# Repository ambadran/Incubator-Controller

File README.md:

# Incubator-Controller

PCB Circuit to interface all the incubator sensors and control all the incubator outputs. Incorporating IOT with Web Interface hosted locally and OLED to monitor everything.

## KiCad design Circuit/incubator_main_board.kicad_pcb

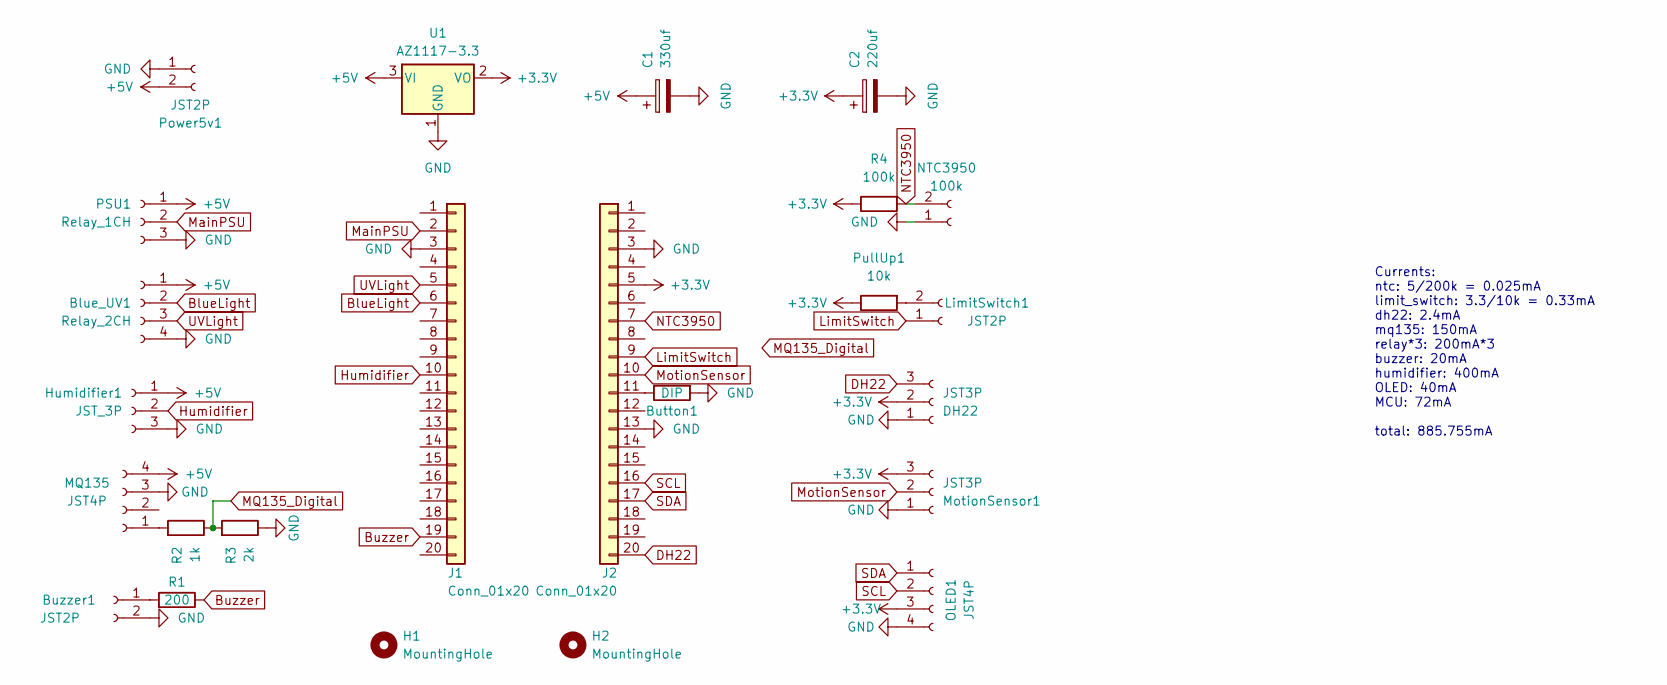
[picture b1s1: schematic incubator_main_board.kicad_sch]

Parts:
Blue_UV1: Relay_2CH; JST_EH_B4B-EH-A_1x04_P2.50mm_Vertical
Button1: DIP; R_Axial_DIN0207_L6.3mm_D2.5mm_P5.08mm_Vertical
Buzzer1: JST2P; JST_EH_B2B-EH-A_1x02_P2.50mm_Vertical
C1: 330uf; CP_Radial_D10.0mm_P5.00mm
C2: 220uf; CP_Radial_D8.0mm_P5.00mm
DH22: JST3P; JST_EH_B3B-EH-A_1x03_P2.50mm_Vertical
H1, H2: MountingHole; MountingHole_4.3mm_M4_DIN965_Pad_TopBottom
Humidifier1: JST_3P; JST_EH_B3B-EH-A_1x03_P2.50mm_Vertical
J1, J2: Conn_01x20; PinSocket_1x20_P2.54mm_Vertical
LimitSwitch1: JST2P; JST_EH_B2B-EH-A_1x02_P2.50mm_Vertical
MQ135: JST4P; JST_EH_B4B-EH-A_1x04_P2.50mm_Vertical
MotionSensor1: JST3P; JST_EH_B3B-EH-A_1x03_P2.50mm_Vertical
NTC3950: 100k; JST_EH_B2B-EH-A_1x02_P2.50mm_Vertical
OLED1: JST4P; JST_EH_B4B-EH-A_1x04_P2.50mm_Vertical
PSU1: Relay_1CH; JST_EH_B3B-EH-A_1x03_P2.50mm_Vertical
Power5v1: JST2P; JST_EH_B2B-EH-A_1x02_P2.50mm_Vertical
PullUp1: 10k; R_Axial_DIN0207_L6.3mm_D2.5mm_P7.62mm_Horizontal
R1: 200; R_Axial_DIN0207_L6.3mm_D2.5mm_P7.62mm_Horizontal
R2: 1k; R_Axial_DIN0207_L6.3mm_D2.5mm_P7.62mm_Horizontal
R3: 2k; R_Axial_DIN0207_L6.3mm_D2.5mm_P7.62mm_Horizontal
R4: 100k; R_Axial_DIN0207_L6.3mm_D2.5mm_P7.62mm_Horizontal
U1: AZ1117-3.3; TO-220-3_Vertical

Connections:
+3.3V: C2.1, DH22.2, J2.5, MotionSensor1.3, OLED1.3, PullUp1.1, R4.1, U1.2 (VO)
+5V: Blue_UV1.1, C1.1, Humidifier1.1, MQ135.4, PSU1.1, Power5v1.2, U1.3 (VI)
BlueLight: Blue_UV1.2, J1.6
Buzzer: J1.19, R1.1
DH22: DH22.3, J2.20
GND: Blue_UV1.4, Button1.2, Buzzer1.2, C1.2, C2.2, DH22.1, Humidifier1.3, J1.3, J2.3, J2.13, MQ135.3, MotionSensor1.1, NTC3950.1, OLED1.4, PSU1.3, Power5v1.1, R3.1, U1.1 (GND)
Humidifier: Humidifier1.2, J1.10
LimitSwitch: J2.9, LimitSwitch1.1
MQ135_Digital: R2.1, R3.2
MainPSU: J1.2, PSU1.2
MotionSensor: J2.10, MotionSensor1.2
NTC3950: J2.7, NTC3950.2, R4.2
unnamed: Buzzer1.1, R1.2
unnamed: Button1.1, J2.11
unnamed: LimitSwitch1.2, PullUp1.2
unnamed: MQ135.1, R2.2
SCL: J2.16, OLED1.2
SDA: J2.17, OLED1.1
UVLight: Blue_UV1.3, J1.5

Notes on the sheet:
Currents: ntc: 5/200k = 0.025mA limit_switch: 3.3/10k = 0.33mA dh22: 2.4mA mq135: 150mA relay*3: 200mA*3 buzzer: 20mA humidifier: 400mA OLED: 40mA MCU: 72mA total: 885.755mA

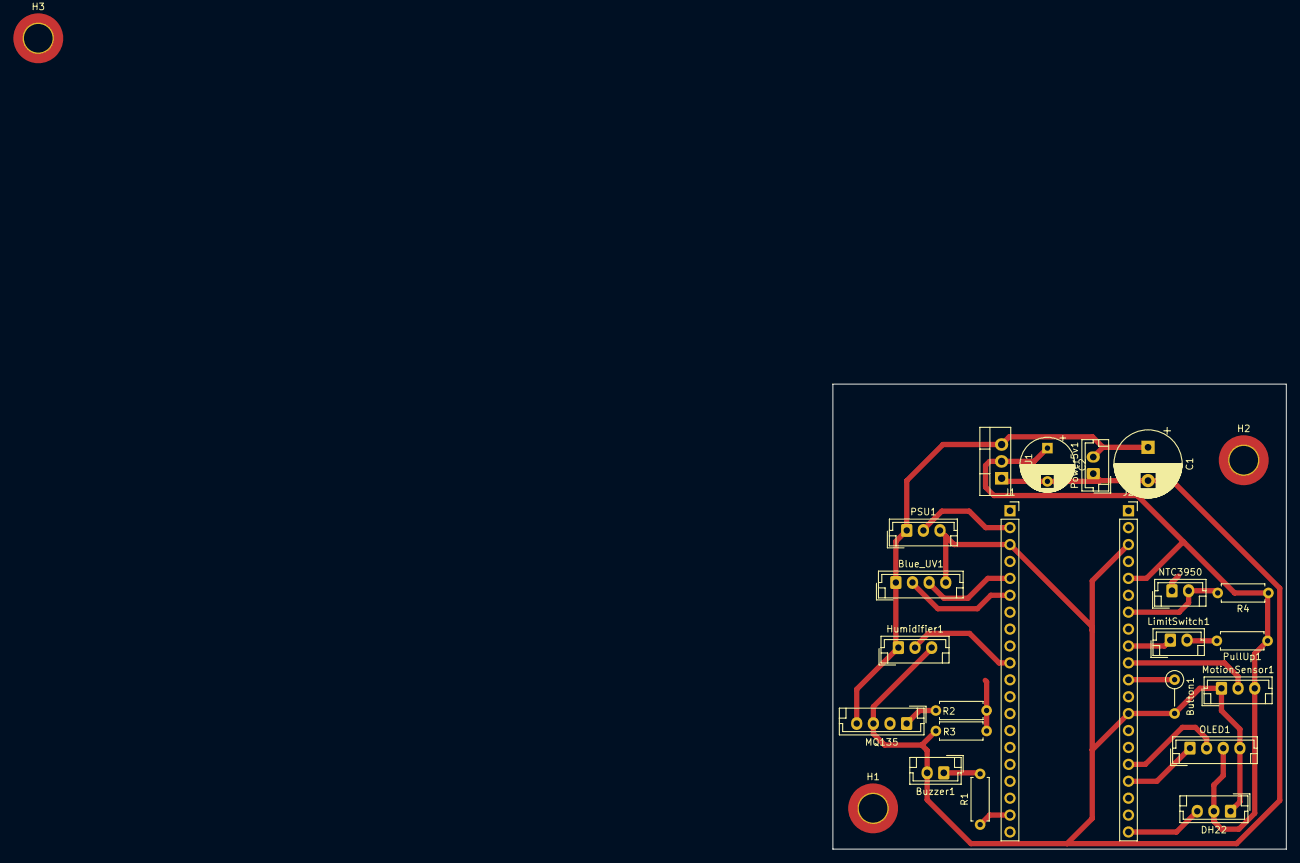
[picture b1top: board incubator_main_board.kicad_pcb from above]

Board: 2 copper layers, 68.1 x 69.8 mm, 25 parts (0 on the bottom side), 19 nets.

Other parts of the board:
H3: MountingHole; MountingHole_4.3mm_M4_DIN965_Pad_TopBottom

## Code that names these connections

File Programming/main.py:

'''
Incubator Controller Main MCU
    -   Read Sensors
    -   Interface Actuators
    -   Control algorithms linking sensor data with actuator actions
    -   Monitor System (oled and web)
'''
from machine import Pin, Timer, I2C
from sensors import Sensors
from actuators import Actuators
from monitor import Monitor
from server2 import Server
from time import sleep
import _thread

print("All System Components Up!\n")

sensors_dict = {
            'skinTemperature': 0,
            'coverClosed': 0,
            'humidity': 0,
            'temperature': 0,
            'motionSensor': 0,
            'o2Level': 0
        }

actuators_dict = {
           'autoManualSwitch': 'off',
           'psuControl': 'off',
           'blueLight': 'off',
           'uvLight': 'off',
           'buzzer': 'off',
           'humidifier': 'off'
       }

def controller_core():
    '''
    Main Routine for the first core which reads the sensor data 
     and controls the actuators
    '''
    global sensors_dict
    global actuators_dict

    sensors = Sensors(
                ntc3950_pin = 28,
                ntc3950_bounds = (23, 28),
                limit_switch_pin = 27,
                limit_switch_bounds = (0 , 0),
                dht22_pin = 16,
                dht22_temp_bounds = (23, 28),
                dht22_humidity_bounds = (40, 60),
                motion_sensor_pin = 26,
                motion_sensor_bounds = (0 ,0),
                mq135_pin = 8,
                mq135_bounds = (1 , 100)  #TODO
                )
    actuators = Actuators(
                    main_psu_pin = 1,
                    blue_light_pin = 3, 
                    uv_light_pin = 4, 
                    buzzer_pin = 14, 
                    humidifier_pin = 7
                    )
    monitor = Monitor(sensors, 19, 18)

    while True:

        # Always read all sensors
        sensors.read_all()
        sensors_dict.update(sensors.all_values)

        # Update Actuators
        actuators.all_values = actuators_dict
        

def server_core():
    '''
    Main Routine for the second core which is hosts a web app to control and monitor the whole system

    '''
    global sensors_dict
    global actuators_dict

    server = Server()
    # display = ssd1306.SSD1306_I2C(128, 64, I2C(1, scl=Pin(19), sda=Pin(18)))
    while True:

        # Send latest sensor data
        server.sensors_dict.update(sensors_dict)

        # Run Server
        server.wait_for_client()
        server.handle_html_request(server.identify_html_request())

        # Receive latest Actuator values
        actuators_dict.update(server.actuators_dict)

        # Toggle LED for User to see
        server.led.toggle()

        print('\n')

def main():
    ### Main Routine  ###
    sleep(5)
    _thread.start_new_thread(controller_core, ())
    sleep(2)
    server_core()


# ### Main Routine  ###
sleep(5)
_thread.start_new_thread(controller_core, ())
sleep(2)
server_core()

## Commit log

2024-06-09 added initial files
2024-06-09 added BOM and circuit schematic
2024-06-10 further development in all components
2024-06-10 finished server implementation and started high level dual core logic
2024-06-10 finished PCB layout
2024-06-10 added PCB pdfs
2024-06-12 finished HAL layer
2024-06-12 finished server code and dual code processing
2024-06-21 minor schematic change
2024-06-22 re-structuring server code with the newest framework
2024-06-25 Web App is now linked to Sensors and Actuators :D
2024-11-06 minor file change
2025-03-08 minor changes
